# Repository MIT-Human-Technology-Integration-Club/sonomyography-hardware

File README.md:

# sonomyography-hardware
Sonomyography CAD and PCB

## Lore Accurate Master Plan

## 90V Flyback Converter
| Schematic | Layout | Render |
| --- | --- | --- |
|  |  |  |

## Ultrasound Pulser
| Schematic | Layout | Render |
| --- | --- | --- |
|  |  | |

## Analog Front End
<table>
<thead>
  <tr><th>Schematic</th><th>Layout</th><th>Render</th></tr>
</thead>
<tbody>
  <tr>
    <td width=33%>
      
    </td>
    <td width=33%>
      
    </td>
    <td width=33%>
      
    </td>
  </tr>
</tbody>
</table>

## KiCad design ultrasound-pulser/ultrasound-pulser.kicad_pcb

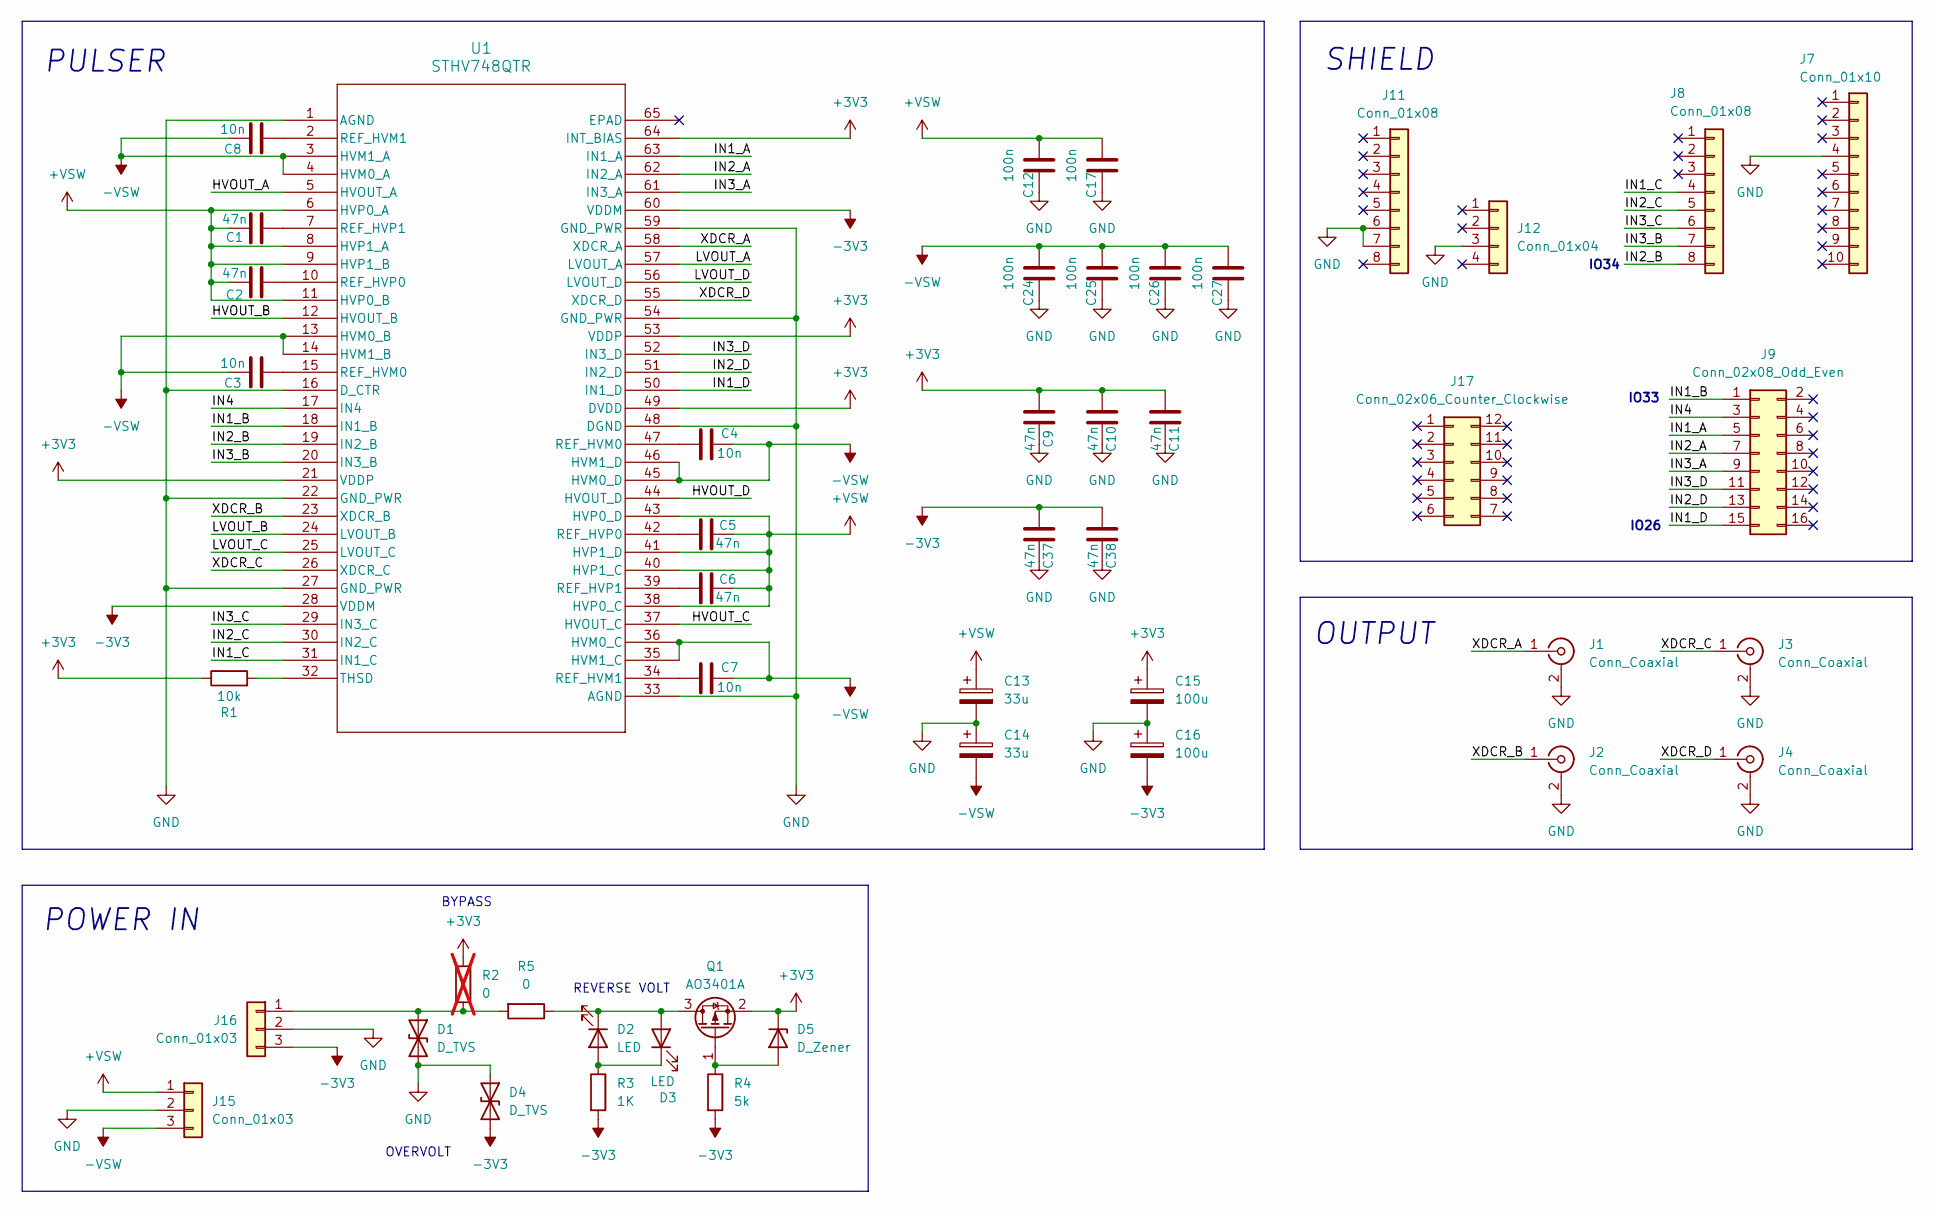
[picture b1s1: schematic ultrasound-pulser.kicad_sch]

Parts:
C1, C2, C5, C6: 47n; C_0805_2012Metric; LCSC C7393958
C3, C4, C7, C8: 10n; C_0603_1608Metric; LCSC C384793
C9, C10, C11, C37, C38: 47n; C_0603_1608Metric; LCSC C1622
C12, C17, C24, C25, C26, C27: 100n; C_1210_3225Metric; LCSC C52020
C13, C14: 33u; CP_Elec_10x12.5; LCSC C22387797
C15, C16: 100u; CP_EIA-3528-21_Kemet-B; LCSC C16133
D1, D4: D_TVS; D_SMB; LCSC C78395
D2, D3: LED; LED_0603_1608Metric; LCSC C2286
D5: D_Zener; D_SOD-123; LCSC C19077406
J1, J2, J3, J4: Conn_Coaxial; BNC_TEConnectivity_1478204_Vertical
J7: Conn_01x10; PinHeader_1x10_P2.54mm_Vertical
J8, J11: Conn_01x08; PinHeader_1x08_P2.54mm_Vertical
J9: Conn_02x08_Odd_Even; PinHeader_2x08_P2.54mm_Vertical
J12: Conn_01x04; PinHeader_1x04_P2.54mm_Vertical
J15: Conn_01x03; AMASS_MR30PW-FB_1x03_P3.50mm_Horizontal
J16: Conn_01x03; JST_EH_B3B-EH-A_1x03_P2.50mm_Vertical
J17: Conn_02x06_Counter_Clockwise; PinHeader_2x06_P2.54mm_Vertical
Q1: AO3401A; SOT-23; LCSC C15127
R1: 10k; R_0603_1608Metric; LCSC C25804
R2: 0; R_0603_1608Metric_Pad0.98x0.95mm_HandSolder; not fitted
R3: 1K; R_0603_1608Metric; LCSC C21190
R4: 5k; R_0603_1608Metric; LCSC C166926
R5: 0; R_0603_1608Metric_Pad0.98x0.95mm_HandSolder; LCSC C21189
U1: STHV748QTR; QFN_748QTR_STM; LCSC C1575208

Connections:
+3V3: C9.2, C10.2, C11.2, C15.1, D5.1 (K), Q1.2 (S), R1.1, R2.2, U1.21 (VDDP), U1.49 (DVDD), U1.53 (VDDP), U1.64 (INT_BIAS)
+VSW: C1.1, C2.2, C5.1, C6.1, C12.1, C13.1, C17.1, J15.1, U1.6 (HVP0_A), U1.8 (HVP1_A), U1.9 (HVP1_B), U1.11 (HVP0_B), U1.38 (HVP0_C), U1.40 (HVP1_C), U1.41 (HVP1_D), U1.43 (HVP0_D)
-3V3: C16.2, C37.2, C38.2, D4.2 (A2), J16.3, R3.2, R4.2, U1.28 (VDDM), U1.60 (VDDM)
-VSW: C3.2, C4.2, C7.2, C8.2, C14.2, C24.1, C25.1, C26.1, C27.1, J15.3, U1.3 (HVM1_A), U1.4 (HVM0_A), U1.13 (HVM0_B), U1.14 (HVM1_B), U1.35 (HVM1_C), U1.36 (HVM0_C), U1.45 (HVM0_D), U1.46 (HVM1_D)
/HVOUT_A: U1.5 (HVOUT_A)
/HVOUT_B: U1.12 (HVOUT_B)
/HVOUT_C: U1.37 (HVOUT_C)
/HVOUT_D: U1.44 (HVOUT_D)
/IN1_A: J9.5, U1.63 (IN1_A)
/IN1_B: J9.1, U1.18 (IN1_B)
/IN1_C: J8.4, U1.31 (IN1_C)
/IN1_D: J9.15, U1.50 (IN1_D)
/IN2_A: J9.7, U1.62 (IN2_A)
/IN2_B: J8.8, U1.19 (IN2_B)
/IN2_C: J8.5, U1.30 (IN2_C)
/IN2_D: J9.13, U1.51 (IN2_D)
/IN3_A: J9.9, U1.61 (IN3_A)
/IN3_B: J8.7, U1.20 (IN3_B)
/IN3_C: J8.6, U1.29 (IN3_C)
/IN3_D: J9.11, U1.52 (IN3_D)
/IN4: J9.3, U1.17 (IN4)
/LVOUT_A: U1.57 (LVOUT_A)
/LVOUT_B: U1.24 (LVOUT_B)
/LVOUT_C: U1.25 (LVOUT_C)
/LVOUT_D: U1.56 (LVOUT_D)
/XDCR_A: J1.1 (In), U1.58 (XDCR_A)
/XDCR_B: J2.1 (In), U1.23 (XDCR_B)
/XDCR_C: J3.1 (In), U1.26 (XDCR_C)
/XDCR_D: J4.1 (In), U1.55 (XDCR_D)
GND: C9.1, C10.1, C11.1, C12.2, C13.2, C14.1, C15.2, C16.1, C17.2, C24.2, C25.2, C26.2, C27.2, C37.1, C38.1, D1.2 (A2), D4.1 (A1), J1.2 (Ext), J2.2 (Ext), J3.2 (Ext), J4.2 (Ext), J7.4 (Pin_4_4), J11.6, J11.7, J12.3 (Pin_3_3), J15.2, J16.2, U1.1 (AGND), U1.16 (D_CTR), U1.22 (GND_PWR), U1.27 (GND_PWR), U1.33 (AGND), U1.48 (DGND), U1.54 (GND_PWR), U1.59 (GND_PWR)
unnamed: C1.2, U1.7 (REF_HVP1)
unnamed: C2.1, U1.10 (REF_HVP0)
unnamed: C3.1, U1.15 (REF_HVM0)
unnamed: C4.1, U1.47 (REF_HVM0)
unnamed: C5.2, U1.42 (REF_HVP0)
unnamed: C6.2, U1.39 (REF_HVP1)
unnamed: C7.1, U1.34 (REF_HVM1)
unnamed: C8.1, U1.2 (REF_HVM1)
unnamed: D1.1 (A1), J16.1, R2.1, R5.2
unnamed: D2.2 (A), D3.1 (K), R3.1
unnamed: D2.1 (K), D3.2 (A), Q1.3 (D), R5.1
unnamed: D5.2 (A), Q1.1 (G), R4.1
unnamed: R1.2, U1.32 (THSD)

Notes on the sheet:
REVERSE VOLT
IO34
SHIELD
PULSER
IO26
OUTPUT
BYPASS
OVERVOLT
POWER IN
IO33

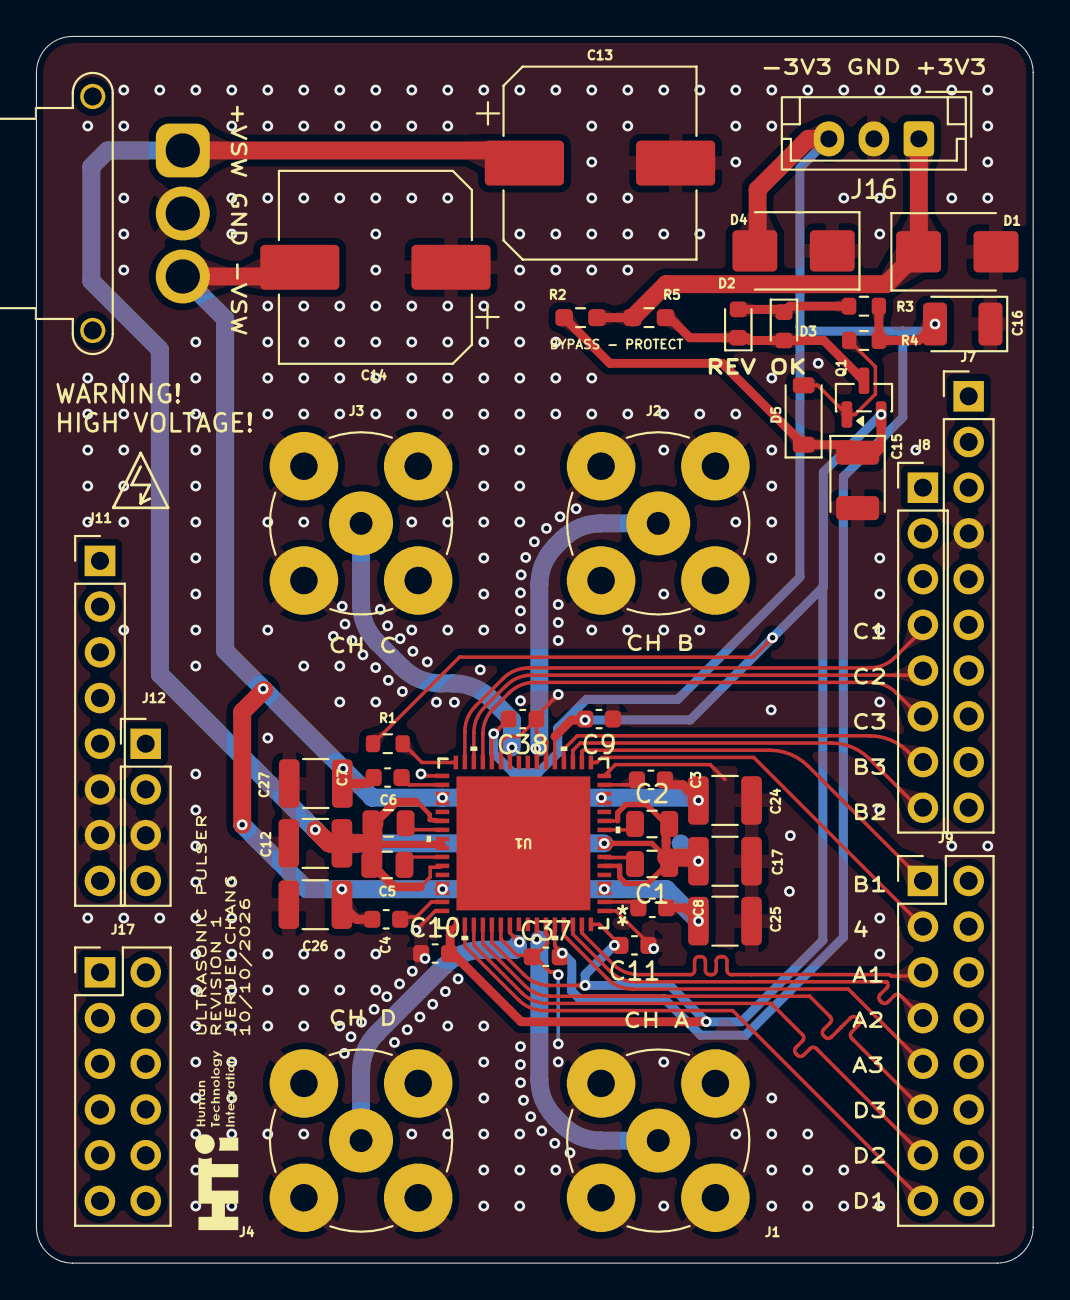
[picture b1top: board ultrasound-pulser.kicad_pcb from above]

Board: 2 copper layers, 55.4 x 68.1 mm, 47 parts (0 on the bottom side), 35 nets.

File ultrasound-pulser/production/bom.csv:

Designator,Footprint,Quantity,Value,LCSC Part #
"C1, C2, C5, C6",0805,4,47n,C7393958
"C10, C11, C37, C38, C9",0603,5,47n,C1622
"C12, C17, C24, C25, C26, C27",1210,6,100n,C52020
"C13, C14",CP_Elec_10x12.5,2,33u,C22387797
"C15, C16",CP_EIA-3528-21_Kemet-B,2,100u,C16133
"C3, C4, C7, C8",0603,4,10n,C384793
"D1, D4",D_SMB,2,D_TVS,C78395
"D2, D3",0603,2,LED,C2286
D5,D_SOD-123,1,D_Zener,C19077406
Q1,SOT-23,1,AO3401A,C15127
R1,0603,1,10k,C25804
R3,0603,1,1K,C21190
R4,0603,1,5k,C166926
R5,0603,1,0,C21189
U1,QFN_748QTR_STM,1,STHV748QTR,C1575208

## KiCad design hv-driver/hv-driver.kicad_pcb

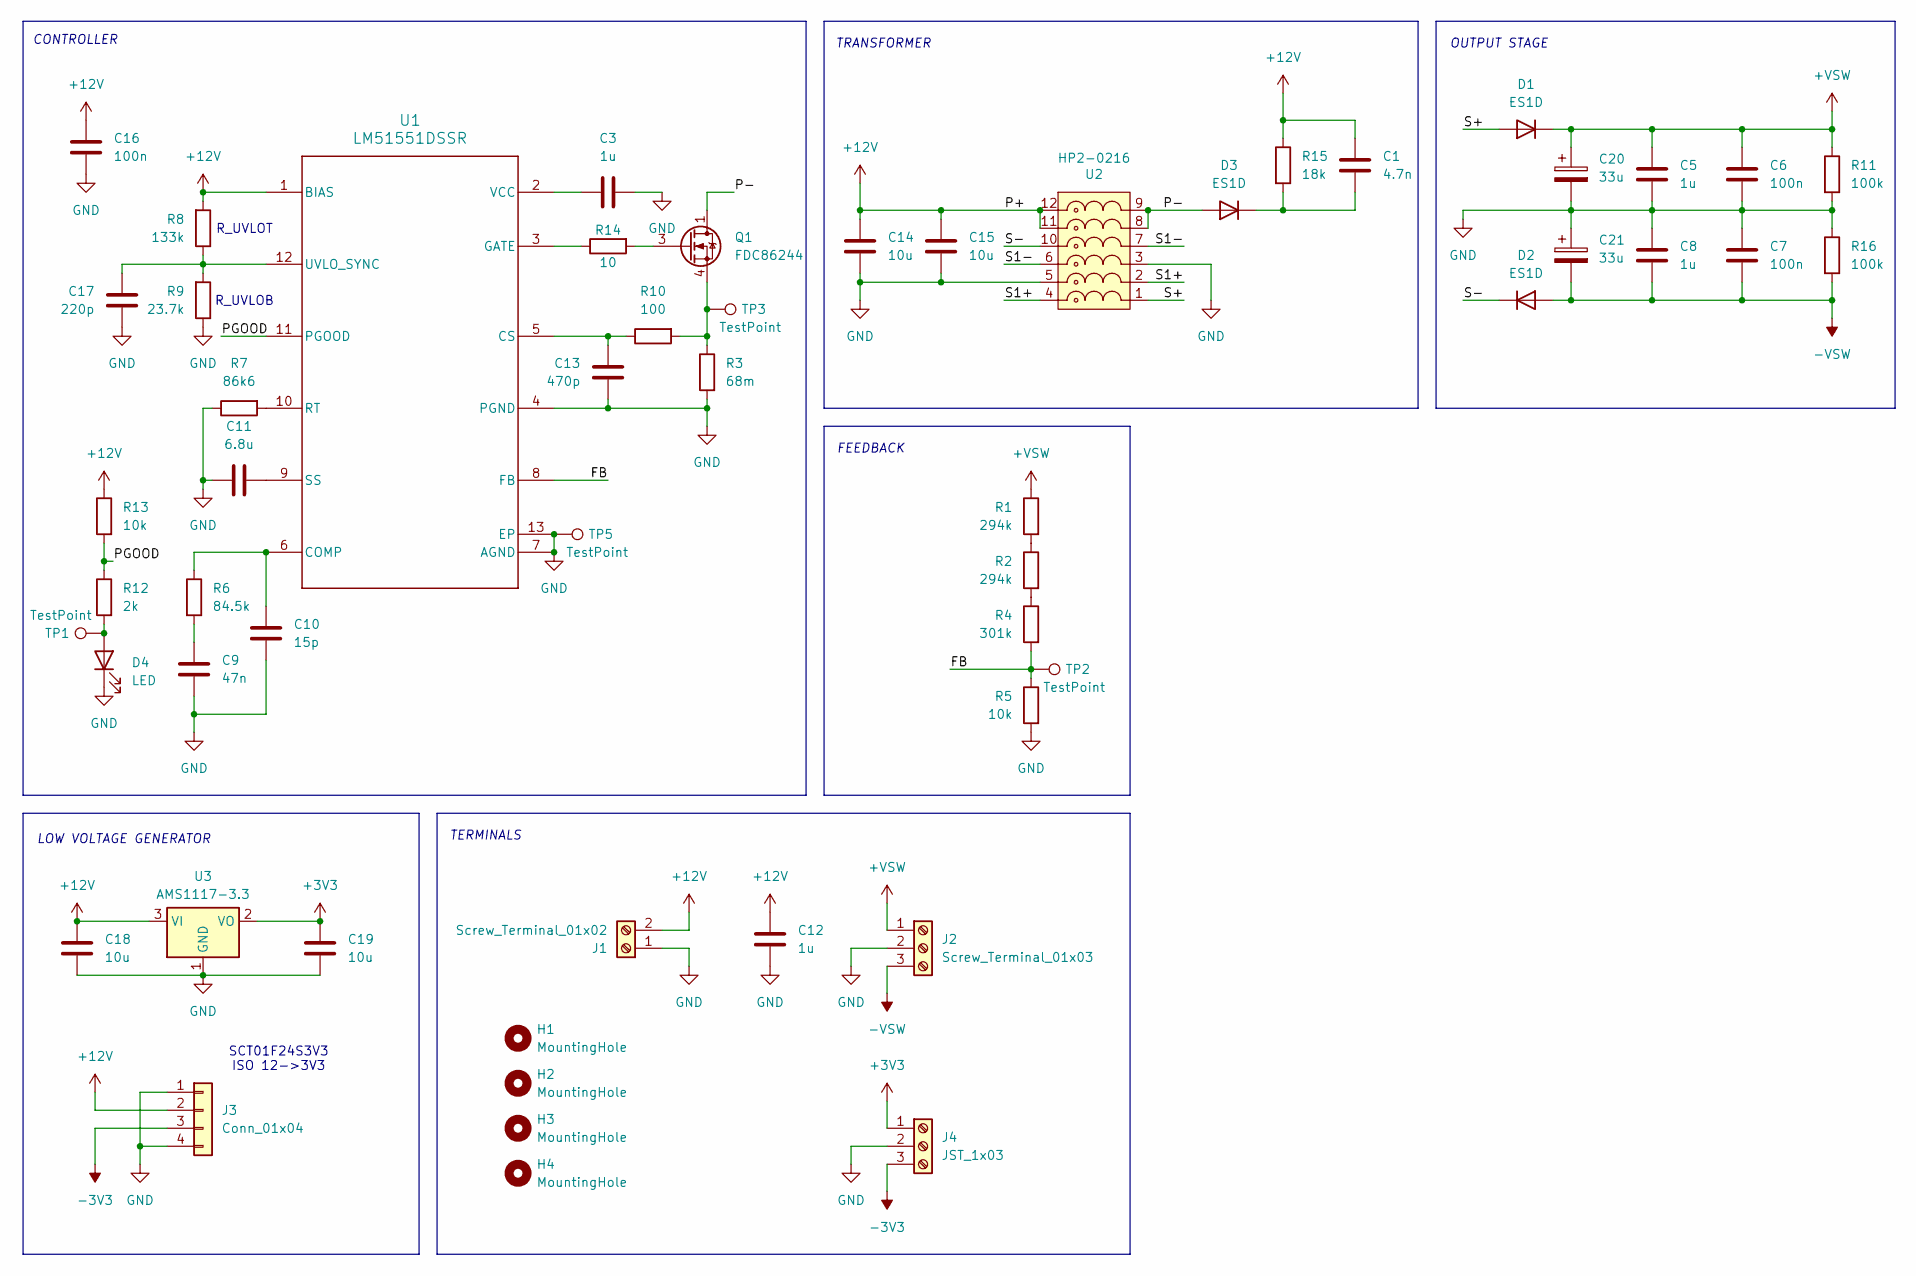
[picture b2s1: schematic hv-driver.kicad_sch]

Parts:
C1: 4.7n; C_0603_1608Metric_Pad1.08x0.95mm_HandSolder; LCSC C53987
C3, C12: 1u; C_0603_1608Metric_Pad1.08x0.95mm_HandSolder; LCSC C15849
C5, C8: 1u; C_1206_3216Metric_Pad1.33x1.80mm_HandSolder; LCSC C1848
C6, C7, C16: 100n; C_0603_1608Metric_Pad1.08x0.95mm_HandSolder; LCSC C14663
C9: 47n; C_0603_1608Metric_Pad1.08x0.95mm_HandSolder; LCSC C1622
C10: 15p; C_0603_1608Metric_Pad1.08x0.95mm_HandSolder; LCSC C1644
C11: 6.8u; C_0603_1608Metric_Pad1.08x0.95mm_HandSolder; LCSC C338096
C13: 470p; C_0603_1608Metric_Pad1.08x0.95mm_HandSolder; LCSC C1620
C14, C15, C18, C19: 10u; C_1206_3216Metric_Pad1.33x1.80mm_HandSolder; LCSC C13585
C17: 220p; C_0603_1608Metric_Pad1.08x0.95mm_HandSolder; LCSC C1603
C20, C21: 33u; CP_Elec_10x12.5; LCSC C22387797
D1, D2, D3: ES1D; D_SMA; LCSC C84602
D4: LED; LED_0603_1608Metric_Pad1.05x0.95mm_HandSolder; LCSC C2286
H1, H2, H3, H4: MountingHole; MountingHole_3.2mm_M3_Pad_Via
J1: Screw_Terminal_01x02; AMASS_XT30U-F_1x02_P5.0mm_Vertical
J2: Screw_Terminal_01x03; AMASS_MR30PW-M_1x03_P3.50mm_Horizontal
J3: Conn_01x04; PinHeader_1x04_P2.54mm_Vertical
J4: JST_1x03; JST_EH_B3B-EH-A_1x03_P2.50mm_Vertical
Q1: FDC86244; SuperSOT-6; LCSC C3290085
R1, R2: 294k; R_0603_1608Metric_Pad0.98x0.95mm_HandSolder; LCSC C25813
R3: 68m; R_2512_6332Metric_Pad1.40x3.35mm_HandSolder; LCSC C2904251
R4: 301k; R_0603_1608Metric_Pad0.98x0.95mm_HandSolder; LCSC C23026
R5, R13: 10k; R_0603_1608Metric_Pad0.98x0.95mm_HandSolder; LCSC C25804
R6: 84.5k; R_0603_1608Metric_Pad0.98x0.95mm_HandSolder; LCSC C23118
R7: 86k6; R_0603_1608Metric_Pad0.98x0.95mm_HandSolder; LCSC C23121
R8: 133k; R_0603_1608Metric_Pad0.98x0.95mm_HandSolder; LCSC C22870
R9: 23.7k; R_0603_1608Metric_Pad0.98x0.95mm_HandSolder; LCSC C22912
R10: 100; R_0603_1608Metric_Pad0.98x0.95mm_HandSolder; LCSC C22775
R11, R16: 100k; R_1206_3216Metric_Pad1.30x1.75mm_HandSolder; LCSC C17900
R12: 2k; R_0603_1608Metric_Pad0.98x0.95mm_HandSolder; LCSC C22975
R14: 10; R_0603_1608Metric_Pad0.98x0.95mm_HandSolder; LCSC C22859
R15: 18k; R_2512_6332Metric_Pad1.40x3.35mm_HandSolder; LCSC C621296
TP1, TP2, TP3, TP5: TestPoint; PinSocket_1x01_P2.54mm_Vertical
U1: LM51551DSSR; DSS0012B; LCSC C778612
U2: HP2-0216; hp2
U3: AMS1117-3.3; SOT-223-3_TabPin2; LCSC C6186

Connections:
+3V3: C19.1, J4.1, U3.2 (VO)
+12V: C1.1, C12.1, C14.1, C15.1, C16.1, C18.1, J1.2, J3.2, R8.2, R13.1, R15.1, U1.1 (BIAS), U2.11, U2.12, U3.3 (VI)
+VSW: C5.1, C6.1, C20.1, D1.1 (K), J2.1, R1.1, R11.1
-3V3: J3.3, J4.3
-VSW: C7.2, C8.2, C21.2, D2.2 (A), J2.3, R16.2
/FB: R4.2, R5.1, TP2.1 (1_1), U1.8 (FB)
/P-: D3.2 (A), Q1.1 (D), Q1.2 (D), Q1.5 (D), Q1.6 (D), U2.8, U2.9
/PGOOD: R12.1, R13.2, U1.11 (PGOOD)
/S1+: U2.2, U2.4
/S1-: U2.6, U2.7
/S+: D1.2 (A), U2.1
/S-: D2.1 (K), U2.10
GND: C3.1, C5.2, C6.2, C7.1, C8.1, C9.2, C10.2, C11.1, C12.2, C13.1, C14.2, C15.2, C16.2, C17.2, C18.2, C19.2, C20.2, C21.1, D4.1 (K), J1.1, J2.2, J3.1, J3.4, J4.2, R3.2, R5.2, R7.1, R9.1, R11.2, R16.1, TP5.1 (1_1), U1.4 (PGND), U1.7 (AGND), U1.13 (EP), U1.14, U1.15, U1.16, U2.3, U2.5, U3.1 (GND)
unnamed: C9.1, R6.2
unnamed: C1.2, D3.1 (K), R15.2
unnamed: D4.2 (A), R12.2, TP1.1 (1_1)
unnamed: Q1.3 (G), R14.2
unnamed: Q1.4 (S), R3.1, R10.2, TP3.1 (1_1)
unnamed: R1.2, R2.1
unnamed: R2.2, R4.1
unnamed: C10.1, R6.1, U1.6 (COMP)
unnamed: C13.2, R10.1, U1.5 (CS)
unnamed: R14.1, U1.3 (GATE)
unnamed: R7.2, U1.10 (RT)
unnamed: C11.2, U1.9 (SS)
unnamed: C17.1, R8.1, R9.2, U1.12 (UVLO_SYNC)
unnamed: C3.2, U1.2 (VCC)

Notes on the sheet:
LOW VOLTAGE GENERATOR
SCT01F24S3V3 ISO 12->3V3
OUTPUT STAGE
TERMINALS
CONTROLLER
R_UVLOB
FEEDBACK
R_UVLOT
TRANSFORMER

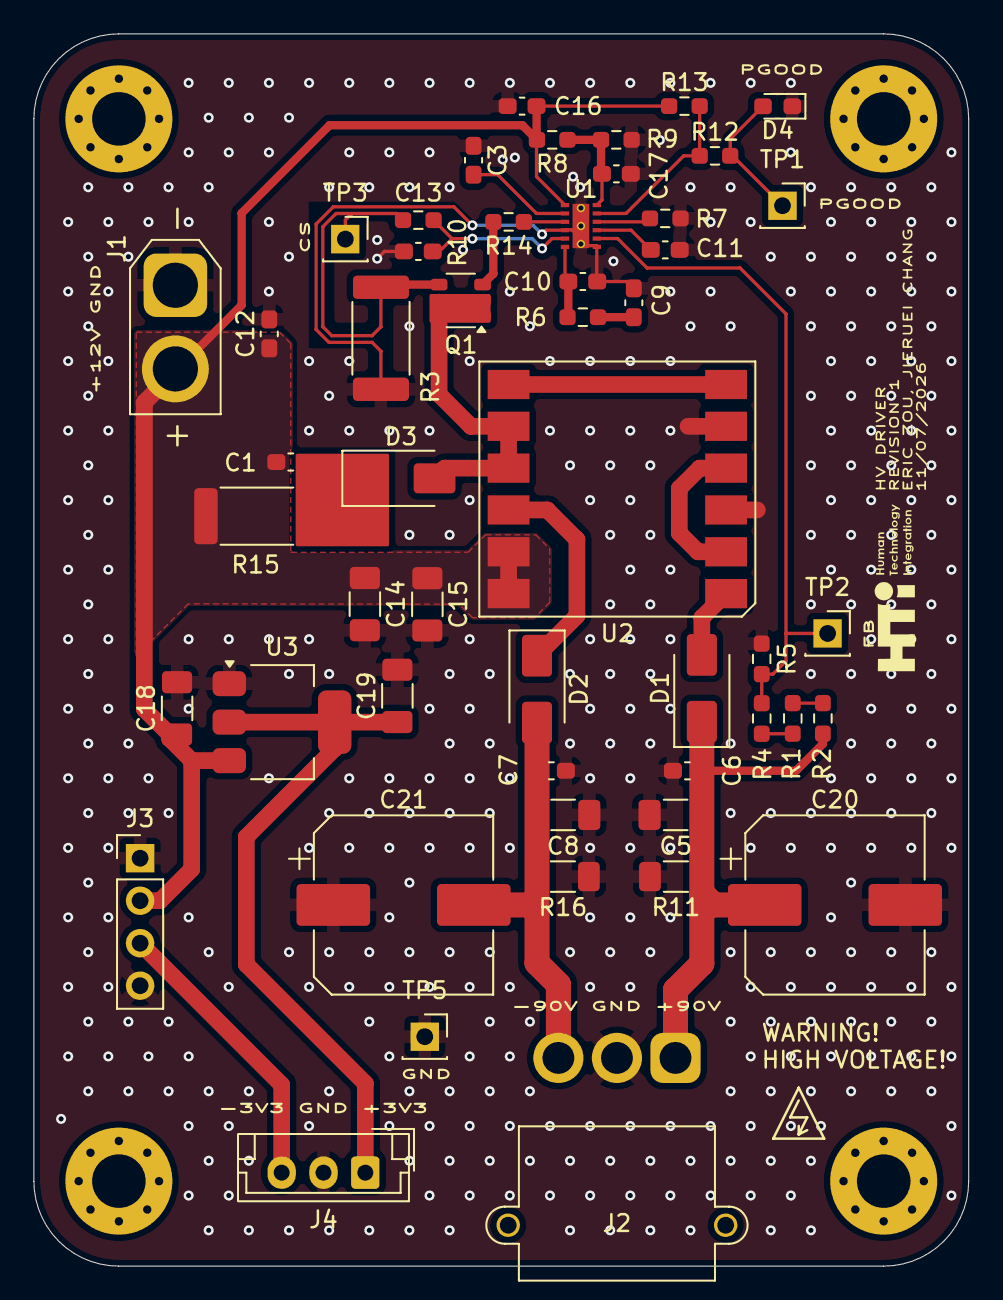
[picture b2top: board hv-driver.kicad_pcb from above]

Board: 2 copper layers, 55.9 x 73.7 mm, 55 parts (0 on the bottom side), 27 nets.

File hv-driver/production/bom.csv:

Designator,Footprint,Quantity,Value,LCSC Part #
C1,0603,1,4.7n,C53987
C10,0603,1,15p,C1644
C11,0603,1,6.8u,C338096
"C12, C3",0603,2,1u,C15849
C13,0603,1,470p,C1620
"C14, C15, C18, C19",1206,4,10u,C13585
"C16, C6, C7",0603,3,100n,C14663
C17,0603,1,220p,C1603
"C20, C21",CP_Elec_10x12.5,2,33u,C22387797
"C5, C8",1206,2,1u,C1848
C9,0603,1,47n,C1622
"D1, D2, D3",D_SMA,3,ES1D,C84602
D4,0603,1,LED,C2286
Q1,SuperSOT-6,1,FDC86244,C3290085
"R1, R2",0603,2,294k,C25813
R10,0603,1,100,C22775
"R11, R16",1206,2,100k,C17900
R12,0603,1,2k,C22975
"R13, R5",0603,2,10k,C25804
R14,0603,1,10,C22859
R15,2512,1,18k,C621296
R3,2512,1,68m,C2904251
R4,0603,1,301k,C23026
R6,0603,1,84.5k,C23118
R7,0603,1,86k6,C23121
R8,0603,1,133k,C22870
R9,0603,1,23.7k,C22912
U1,DSS0012B,1,LM51551DSSR,C778612
U3,SOT-223-3_TabPin2,1,AMS1117-3.3,C6186

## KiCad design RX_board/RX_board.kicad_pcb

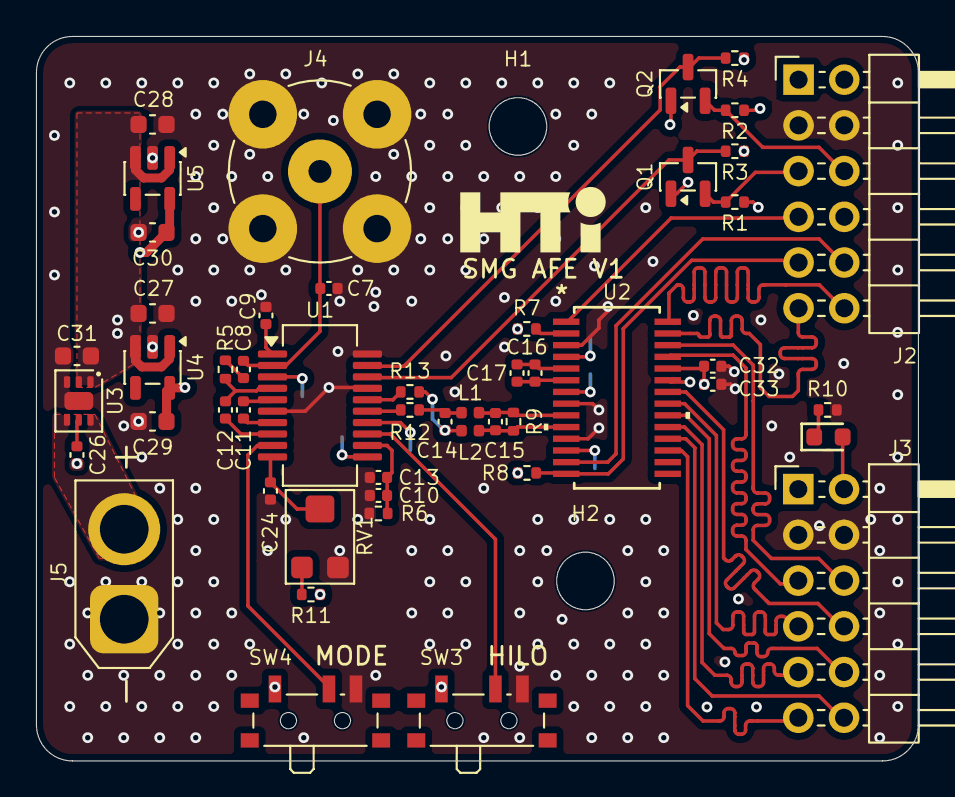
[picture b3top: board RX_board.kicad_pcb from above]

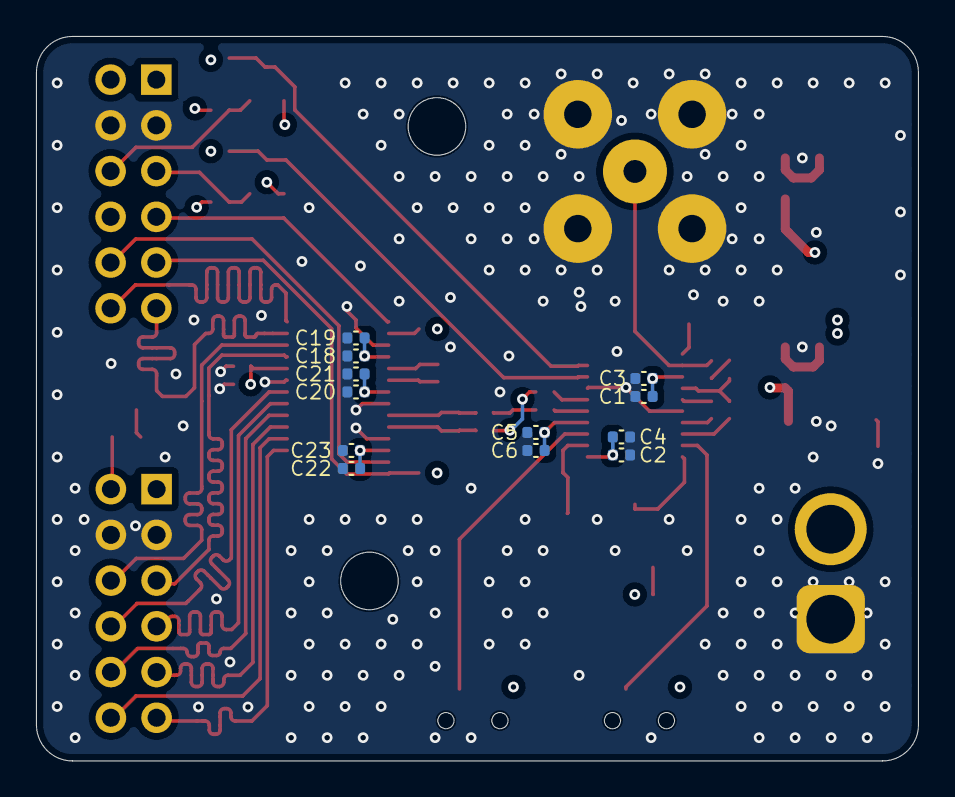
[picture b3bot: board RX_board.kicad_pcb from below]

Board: 4 copper layers, 49.0 x 40.2 mm, 64 parts (12 on the bottom side), 47 nets.

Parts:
C1, C2, C5, C8, C9, C10, C11, C12, C16, C18, C20, C22, C32: 0.1u; C_0402_1005Metric
C3, C4, C6, C13, C17, C19, C21, C23, C24, C26, C33: 1n; C_0402_1005Metric
C7: 22p; C_0402_1005Metric
C14, C15: 16p; C_0402_1005Metric
C27, C28, C29, C30: 1u; C_0603_1608Metric
C31: 2.2u; C_0603_1608Metric
D1: Red; D_0603
H1, H2: MountingHole; MountingHole_3.2mm_M3_DIN965
J2, J3: HC-PM254-8.5H-2x6PW; PinHeader_2x06_P2.54mm_Horizontal
J4: Conn_Coaxial; BNC_TEConnectivity_1478204_Vertical
J5: Conn_01x02; AMASS_XT30U-F_1x02_P5.0mm_Vertical
L1, L2: 640n; L_0402_1005Metric
Q1, Q2: 2N7002; SOT-23
R1, R2, R3, R4, R7, R8: 10k; R_0402_1005Metric
R5: 280R; R_0402_1005Metric
R6: 7.5k; R_0402_1005Metric
R9: 200R; R_0402_1005Metric
R10: 1k; R_0402_1005Metric
R11: 39k; R_0402_1005Metric
R12, R13: 100R; R_0402_1005Metric
RV1: TC33X-2-103E; Potentiometer_Bourns_TC33X_Vertical
SW3, SW4: SW_SPDT; SW_SPDT_PCM12
U1: AD8331; QSOP-20_3.9x8.7mm_P0.635mm
U2: AD9215BRUZ-105; RU_28_ADI
U3: ADP7118ACPZN5.0; DFN-6-1EP_2x2mm_P0.65mm_EP1x1.6mm
U4: TPS7A2030PDBVR; SOT-23-5
U5: TPS7A2033PDBVR; SOT-23-5

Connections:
+1V8A: C2.1, C4.1, C30.1, U1.11 (VCM), U5.5 (OUT)
+3V3: C32.1, C33.1, D1.2, J2.1, J2.2, J3.1, J3.2, Q1.1 (G), Q2.1 (G), R1.1, R2.1, R8.1, U2.24 (DRVDD)
+3VA: C20.1, C21.1, C22.1, C23.1, C29.1, R7.1, U2.7 (AVDD), U2.12 (AVDD), U4.5 (OUT)
+5V: C1.1, C3.1, C5.1, C6.1, C27.1, C28.1, C31.1, R3.1, R4.1, R11.1, SW3.1 (A), SW4.1 (A), U1.3 (VPSL), U1.14 (VPOS), U3.1 (OUT), U3.2 (SENSE), U4.1 (IN), U4.3 (EN), U5.1 (IN), U5.3 (EN)
+12V: J5.2, U3.4 (EN), U3.6 (IN)
/ADC/D0: J3.11, U2.17 (D0_LSB)
/ADC/D1: J3.12, U2.18 (D1)
/ADC/D2: J3.9, U2.19 (D2)
/ADC/D3: J3.10, U2.20 (D3)
/ADC/D4: J3.7, U2.21 (D4)
/ADC/D5: J3.8, U2.22 (D5)
/ADC/D6: J3.5, U2.25 (D6)
/ADC/D7: J3.6, U2.26 (D7)
/ADC/D8: J2.11, U2.27 (D8)
/ADC/D9: J2.12, U2.28 (D9_MSB)
/ADC/MODE: R7.2, U2.2 (MODE)
/ADC/REFB: C16.1, C17.1, U2.5 (REFB)
/ADC/REFT: C16.2, C17.2, U2.6 (REFT)
/ADC/VIH: R12.1, U1.15 (VOH)
/ADC/VIL: R13.1, U1.16 (VOL)
/ADC/VIN: C15.2, L2.2, R9.2, U2.10 (VIN-)
/ADC/VIP: C15.1, L1.2, R9.1, U2.9 (VIN+)
/FPGA/CLK: J2.10, U2.13 (CLK)
/FPGA/ENBL: J2.6, Q2.2 (S), R2.2
/FPGA/ENBV: J2.5, Q1.2 (S), R1.2
/FPGA/OR: J2.7, U2.1 (OR)
/FPGA/~PWDN: J2.9, R8.2, U2.14 (PDWN)
/Input/OUT: C7.2, C8.1, J4.1 (In), U1.2 (INH)
/VGA/GAIN: C24.1, RV1.2, U1.10 (GAIN)
/VGA/VIN: C12.2, U1.8 (VIN)
/VGA/VIP: C11.2, U1.7 (VIP)
GND: C1.2, C2.2, C3.2, C4.2, C5.2, C6.2, C7.1, C9.2, C10.2, C13.2, C18.2, C19.2, C20.2, C21.2, C22.2, C23.2, C24.2, C26.2, C27.2, C28.2, C29.2, C30.2, C31.2, C32.2, C33.2, J2.3, J2.4, J3.3, J3.4, J4.2 (Ext), J5.1, R6.2, R10.2, RV1.3, SW3.3 (C), SW4.3 (C), U1.6 (COML), U1.17 (COMM), U1.20 (COMM), U2.3 (SENSE), U2.8 (AGND), U2.11 (AGND), U2.23 (DRGND), U3.3 (GND), U3.7 (EP), U4.2 (GND), U5.2 (GND)
unnamed: C8.2, R5.1
unnamed: C14.1, L1.1, R12.2
unnamed: C14.2, L2.1, R13.2
unnamed: D1.1, R10.1
unnamed: Q1.3 (D), R3.2, U1.18 (ENBV)
unnamed: Q2.3 (D), R4.2, U1.19 (ENBL)
unnamed: R11.2, RV1.1
unnamed: SW3.2 (B), U1.13 (HILO)
unnamed: SW4.2 (B), U1.9 (MODE)
unnamed: C9.1, U1.1 (LMD)
unnamed: C12.1, R5.2, U1.4 (LON)
unnamed: C11.1, U1.5 (LOP)
unnamed: C10.1, C13.1, R6.1, U1.12 (RCLMP)
unnamed: C18.1, C19.1, U2.4 (VREF)
unnamed: C26.1, U3.5 (SS)

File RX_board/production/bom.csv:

Designator,Footprint,Quantity,Value,LCSC Part #
"C1, C10, C11, C12, C16, C18, C2, C20, C22, C32, C5, C8, C9",0402,13,0.1u,C307331
"C13, C17, C19, C21, C23, C24, C26, C3, C33, C4, C6",0402,11,1n,C1523
"C14, C15",0402,2,16p,C48836
"C27, C28, C29, C30",0603,4,1u,C15849
C31,0603,1,2.2u,C23630
C7,0402,1,22p,C1555
D1,D_0603,1,Red,C2286
"J2, J3",PinHeader_2x06_P2.54mm_Horizontal,2,HC-PM254-8.5H-2x6PW,
J4,BNC_TEConnectivity_1478204_Vertical,1,Conn_Coaxial,
J5,AMASS_XT30U-F_1x02_P5.0mm_Vertical,1,Conn_01x02,
"L1, L2",0402,2,640n,C711175
"Q1, Q2",SOT-23,2,2N7002,C8545
"R1, R2, R3, R4, R7, R8",0402,6,10k,C25744
R10,0402,1,1k,C11702
R11,0402,1,39k,C25783
"R12, R13",0402,2,100R,C25076
R5,0402,1,280R,C159052
R6,0402,1,7.5k,C25918
R9,0402,1,200R,C25087
RV1,Potentiometer_Bourns_TC33X_Vertical,1,TC33X-2-103E,C719176
"SW3, SW4",SW_SPDT_PCM12,2,SW_SPDT,C221841
U1,QSOP-20_3.9x8.7mm_P0.635mm,1,AD8331,C203731
U2,RU_28_ADI,1,AD9215BRUZ-105,C386303
U3,DFN-6-1EP_2x2mm_P0.65mm_EP1x1.6mm,1,ADP7118ACPZN5.0,C659349
U4,SOT-23-5,1,TPS7A2030PDBVR,C963429
U5,SOT-23-5,1,TPS7A2033PDBVR,C2862740
